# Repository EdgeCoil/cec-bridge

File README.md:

# cec-bridge

An HDMI-CEC and IR bridge for Home Assistant: an ESP32-C3 running ESPHome that plugs into a spare
port on a TV or AV receiver, talks CEC, and blasts and learns IR. 40 × 48 mm, two layers, every
part placed by the assembler.

- [`cec-bridge/`](cec-bridge/): the board, its generator and build, and the full README (what it
  does, how to build and order it, bring-up checks, firmware notes, credits and licence).
- [`vendor/`](vendor/): the [edgecoil-pcb](https://github.com/EdgeCoil/edgecoil-pcb) toolkit the
  board is built with, vendored so the board builds on its own.

Not yet built: the design is reviewed and simulated, but no boards have been ordered.

HDMI is a trademark of HDMI Licensing Administrator, Inc. This is an independent design, not a
licensed HDMI product.

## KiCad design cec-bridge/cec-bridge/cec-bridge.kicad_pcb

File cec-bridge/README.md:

# cec-bridge

An HDMI-CEC and IR bridge for Home Assistant: an ESP32-C3-WROOM-02 running ESPHome
(`Palakis/esphome-hdmi-cec`), on a short HDMI cable into a spare port on the TV or receiver. It
speaks CEC only (pin 13), reads hot-plug detect (pin 19) and can put +5 V on pin 18 for sinks that
only listen on a port that sees it. TMDS and DDC are not connected: no video, no EDID. It also blasts
IR (an on-board 940 nm LED and a JST-PH socket for a stick-on emitter) and has an IR receiver for
learning codes. Power is USB-C from a 5 V wall charger rated 1 A or more, on an always-on socket,
that holds USB's 4.75–5.25 V (simulated to 5.5 V: past 5.25 V pin 18 exceeds HDMI's 5.3 V, and a
contact bounce with pin 18 on can ring it to U6's 7 V limit).
Not the TV's or receiver's USB port: those give 500 mA and often switch off in standby, and Wi-Fi
transmit, IR and pin 18 together peak near 0.6 A (about 0.9 A with pin 18 shorted).

40 × 48 mm, two layers, every part on the top and placed by JLC; nothing to hand-solder.

## Build

```
KICAD_SYMBOL_DIR=~/.local/share/kicad-symbols/x/usr/share/kicad/symbols ./build.sh
```

`gen.py` writes the schematic and board, `route.py` replays the frozen routing in
`cec-bridge/routing.json` (move it aside to autoroute again, only after a placement change), and `build.sh` runs ERC/DRC
and writes JLC's BOM and placement files to `cec-bridge/fab/`. Reviewed in audit rounds until one came back clean, then simulated with the routed copper.

## Ordering

- JLC Standard PCBA, top side. If JLC adds rails, they go on the left and right edges: the module
  antenna overhangs the top edge and the USB-C face the bottom edge (by 0.46 mm).
- JLC's DFM check flags the USB-C shell slots (0.6 mm, below its 0.61 mm alert). They are the
  connector's own figure and JLC drills them; the alert is expected.
- The board edge runs about 0.3 mm past the HDMI socket's face (the USB-C face sits 0.46 mm proud of
  its edge). A plug's moulding tolerates about 1 mm of recess, so an enclosure wall in front of the
  socket should be thin there; seat a real cable at bring-up.
- H1 (the M2 hole beside the switches) has a 3V3 track 1.6 mm from its centre on the top, under
  mask: **nothing metal on the top there** — a nylon screw head, washer or
  standoff, or insert the screw from the back with a nylon washer on top. On the back the nearest
  copper is a 3V3 via 2.7 mm out (track 2.8 mm), so an M2 nut, 4 mm pan head or 4 mm hex standoff is
  fine on that side; not a washer (a DIN 125 sitting off-centre reaches the via).
- H2 has a VBUS track 2.85 mm from its centre on the top and ground otherwise: the same hardware as
  H1's back (M2 nut, 4 mm pan head or hex standoff), no metal washer on the top.
- The HDMI socket is held by its four shell legs. The enclosure should back the socket so plugging
  a cable in doesn't lever the board on its two M2 screws.
- **Stock, re-queried 2026-10-30.** U6 is a **TPS25200DRVT (C2653855)**: 484 listed, 167 orderable.
  The DRVR (C128401) listed 79 but was oversold (JLC's orderable figure -664; LCSC stock 0). Same part,
  small reel. J3 is an XYECONN XY-S2B-PH-SM4-TB (C54582899, about 5,000 orderable), a JST-PH-compatible
  2-pin SMD header; JST's own S2B-PH-SM4-TB (C295747) was down to 2. Every other line had at least
  6,397. **Check U6's orderable number (not the listed stock) before paying.**
- JLC's DFM check may flag same-net copper within 0.07 mm of a few pad openings: C11.1's opening is
  0.010 mm from its own VBUS track (also C10.2, C5.2 at 0.041 mm and TP1 at 0.051 mm). Same net,
  connected: expected.

## Bring-up checks

1. **Unpowered, it must not load the CEC bus** (HDMI 1.4: at most 1.8 µA). Every part on the line
   is chosen on its guaranteed figure: D1 is a BAV170 (a BAT54C passed 1.8 µA from about 37 °C in
   simulation) and the ESD array U3 a TPD4E1U06 (10 nA maximum at 2.5 V, where an SRV05-4 is specified to 5 µA;
   CEC idles at 3.3 V, far below its 6.5 V minimum breakdown).
   Unpowered, feed pin 13 from 3.3 V through 27 kΩ: the drop across the resistor must be under 49 mV.
2. **3V3 during Wi-Fi transmit:** scope it at the regulator and at the module. The output capacitance
   (C4, C5 and the module's own) is above the 22 µF ST characterises the LDL1117's stability for; the
   copper brings the ESR inside its range, and simulation can't prove the phase margin. Look for
   ringing on power-up and on a Wi-Fi burst, with a ground spring. Both capacitors are unlabelled:
   - **At the regulator:** C4 is the 0805 just above U5, left of R25 (the labelled 0603). **Don't
     probe across C4:** its right pad is its return (net C4_ESR), which reaches ground only through
     R25, so once R25 is swapped the probe would miss the ringing. Probe from C4's left pad (3V3) to
     R25's right pad (GND), 5.2 mm apart; U5's pin 1 (GND), 5.0 mm away, also works.
   - **At the module:** C5 is the 0603 in the top-left corner, left of the module's pin 1; its upper
     pad is GND and its lower pad 3V3, 1.55 mm apart.

   If 3V3 rings or oscillates, **swap R25** (0 Ω, in C4's return) for 0.1–0.47 Ω: that puts C4's ESR
   well inside ST's Fig. 20/21 region without a new board. Use tweezers or an iron, not hot air: C4's
   pad is 0.78 mm away and would lift too. Re-scope after the swap. If that is not enough, ST's other
   lever is C4 down to 4.7–10 µF.
3. **Pin 18 with the switch on** follows VBUS to within about 10 mV (U6, a TPS25200, is a 60 mΩ
   switch), so it is the charger's voltage: USB allows 4.75–5.25 V, so only a charger at the very
   bottom of that range puts it under HDMI's 4.8 V minimum. U6 limits the current to 240–350 mA
   (R24 330k; HDMI asks for at most 0.5 A), soft-starts in 2–3 ms, and never back-feeds VBUS while
   off (while on it conducts both ways: a sink driving pin 18 can feed the board). On a held short it
   holds the limit and cycles on its thermal shutdown; the instant a short lands, VBUS dips for
   microseconds while U6's limit catches up (sim4: 3V3 down to 3.03 V on the real copper, below
   3.0 V in a lumped model), so the ESP32 may reset once. That is acceptable for a fault.
   Its input is rated to 20 V, so VBUS ringing to about 9 V at plug-in can't hurt it; above
   6.8–8.45 V it disconnects pin 18, and it clamps pin 18 at 5.25–5.55 V.
   R16 holds it off through reset (IO5 has no pull of its own). Check: switch it on into a real sink,
   then short pin 18 to ground through an ammeter while scoping 3V3 at the module: about
   0.24–0.35 A once settled, and the board running (at most one reset as the short lands).
4. **IR**: the external emitter plugs into J3 with its anode on the pin marked "+" (pin 1, fed from
   VBUS through R20); JST-PH lead colours aren't consistent between suppliers. Each LED takes about 80 mA pulses through 47 Ω. The receiver sits 6 mm from the on-board
   LED and hears its own transmissions; ignore received codes while transmitting.

## Firmware notes

- Keep ESPHome's brown-out detector on (the default): a dropout of a few ms takes 3V3 low without
  EN ever resetting the chip.
- IR transmit: `carrier_duty_percent: 33` (ESPHome defaults to 50), which keeps R19 and R20 inside
  their 1/8 W even within a long burst.
- Debounce HPD (IO6, active low) for a few hundred ms: with a hot, low-threshold Q4 a source low
  near 0.6 V can read as half-asserted.

## Credits and licence

The footprints, symbols and 3D models in `lib/` (the HDMI socket, IR receiver, 2835 IR LED and
SOT-223 parts, and the `cb` symbols) come from the JLCEDA/EasyEDA official library
([lceda.cn](https://lceda.cn), [easyeda.com](https://easyeda.com)), converted with `easyeda2kicad`.
The 3D models are not included: fetch them with `easyeda2kicad --3d --lcsc_id=<part> --output lib/cb`
for the LCSC part numbers in the BOM.

The board design is CERN-OHL-S-2.0 and the scripts MIT, as each file's header says; `vendor/` is
the MIT-licensed [edgecoil-pcb](https://github.com/EdgeCoil/edgecoil-pcb) toolkit. The edgecoil name
and mark are not licensed.

HDMI, the HDMI logo and High-Definition Multimedia Interface are trademarks or registered trademarks
of HDMI Licensing Administrator, Inc. This is an independent hobby design, not a licensed HDMI
product, and is not affiliated with or endorsed by HDMI Licensing Administrator.

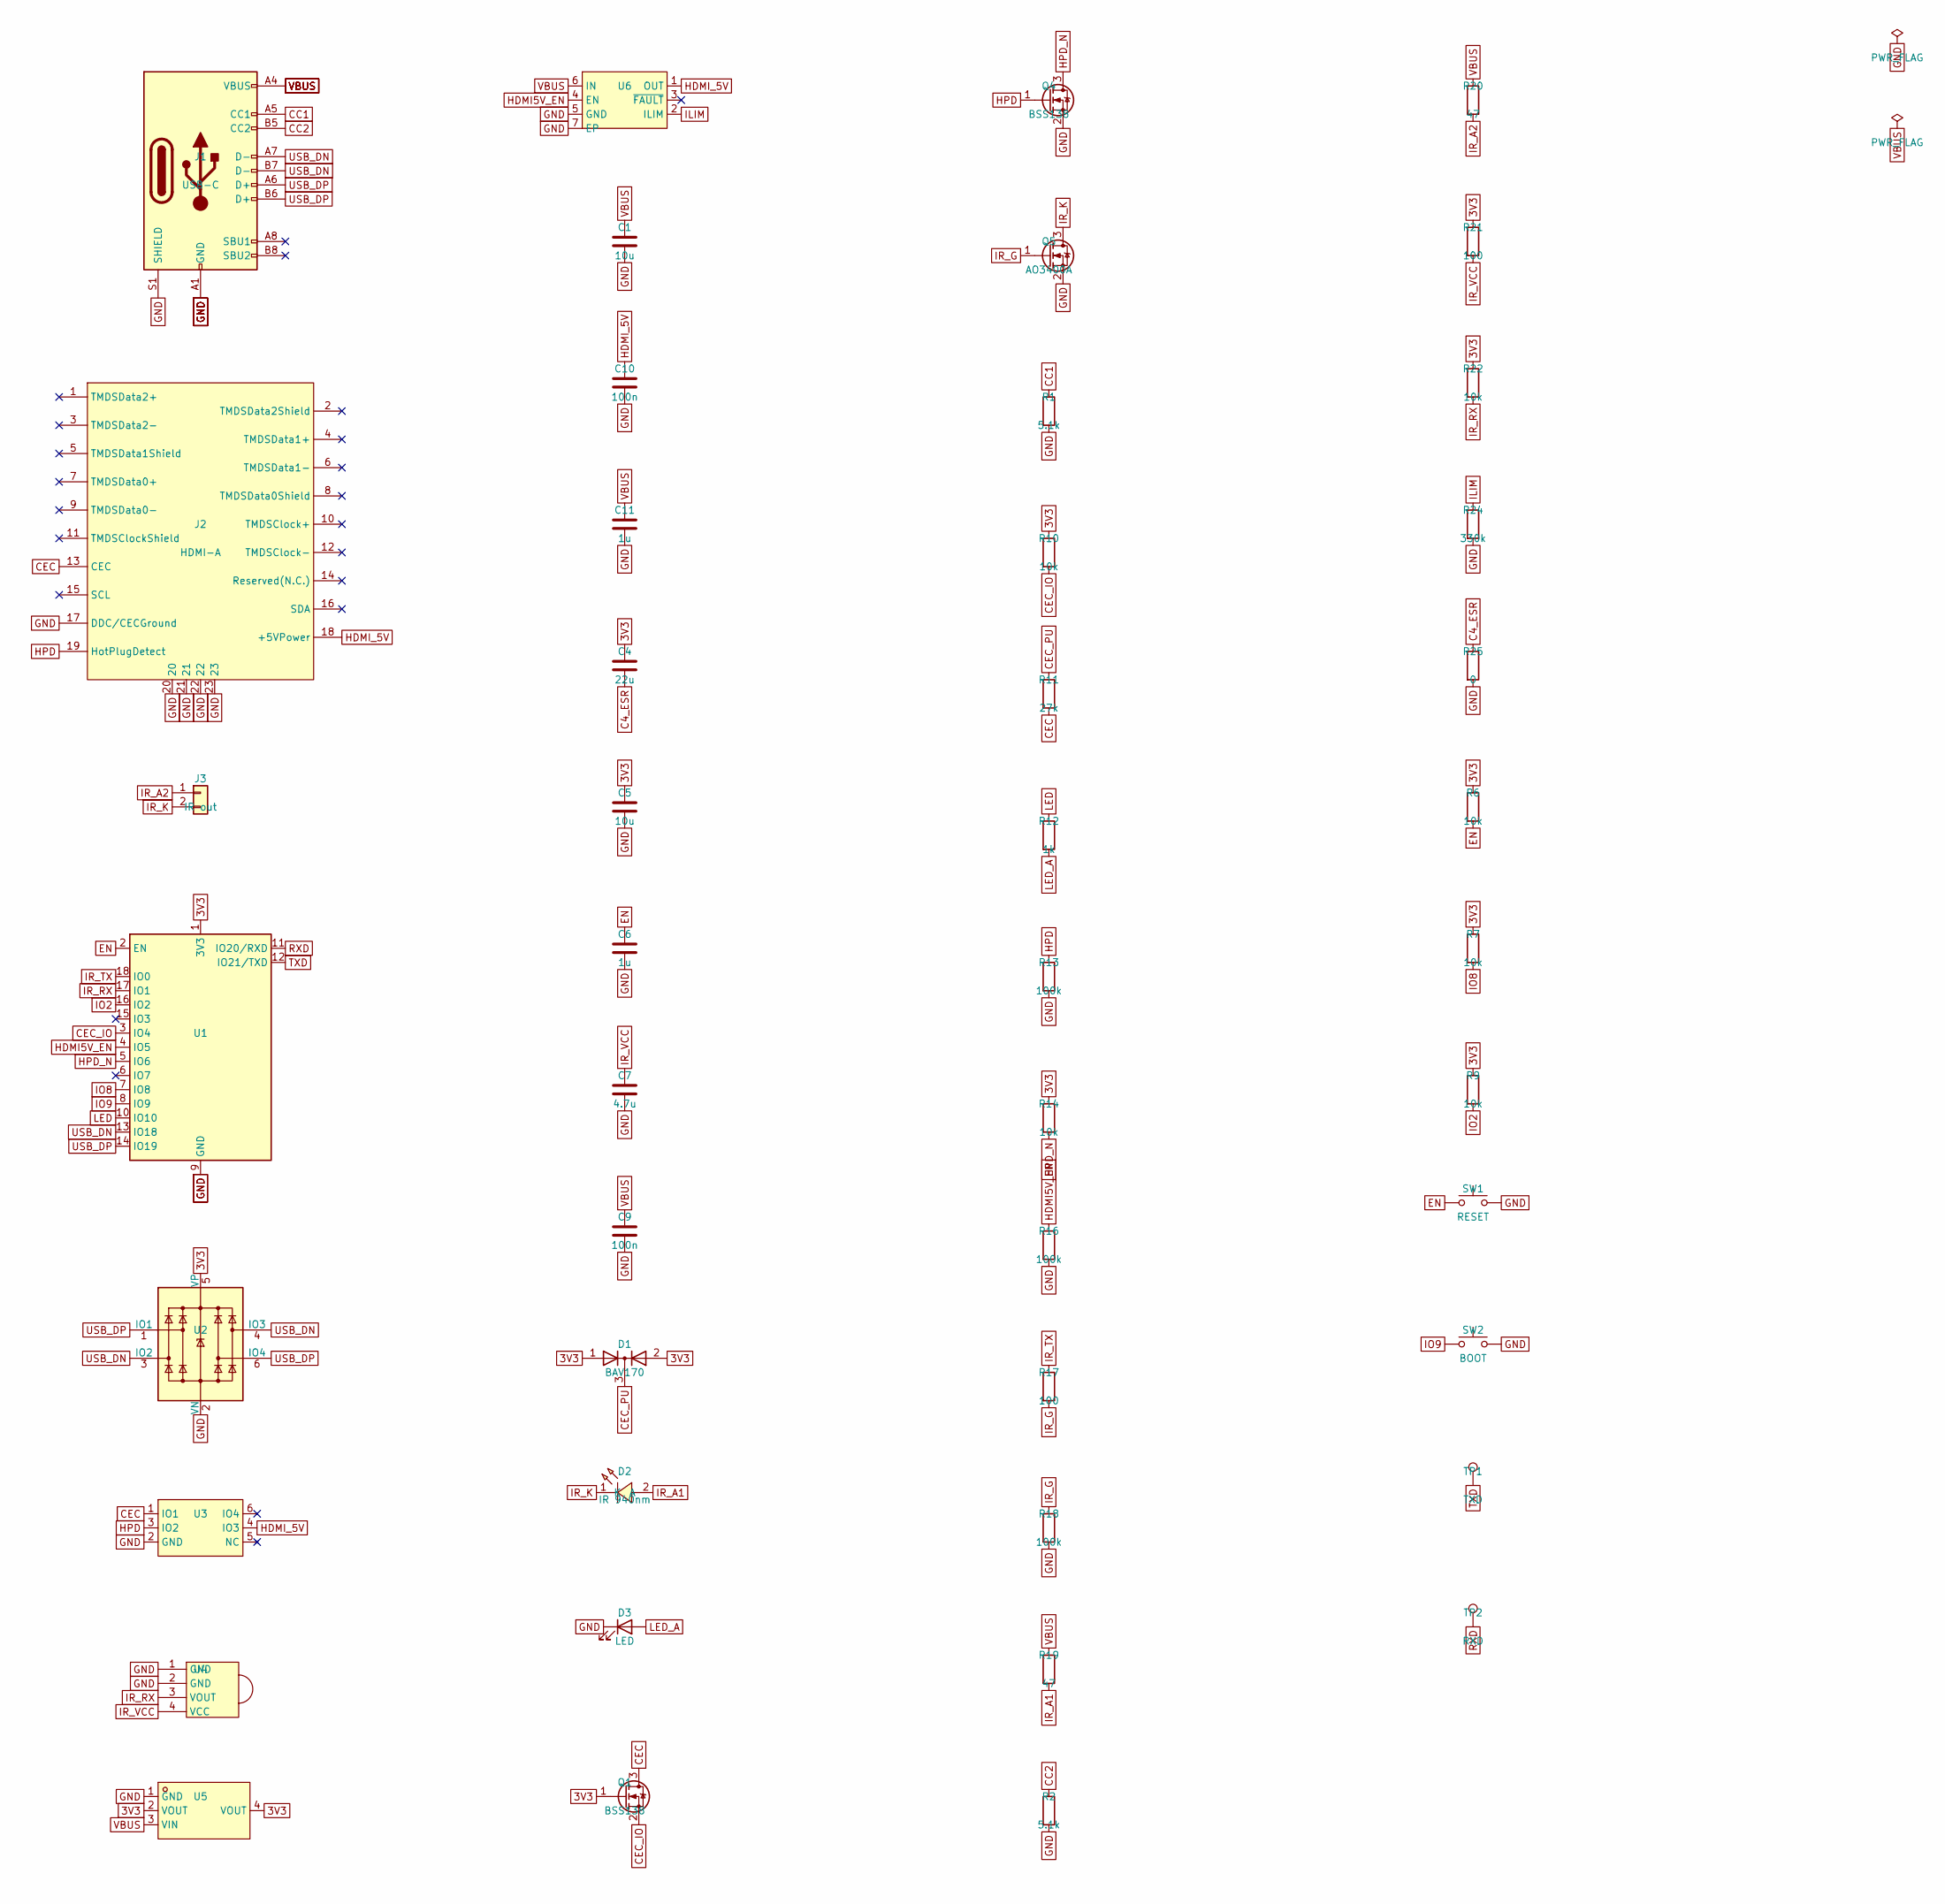
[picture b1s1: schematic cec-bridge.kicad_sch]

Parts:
C1: 10u; C_0805_2012Metric; LCSC C15850
C4: 22u; C_0805_2012Metric; LCSC C45783
C5: 10u; C_0603_1608Metric; LCSC C19702
C6, C11: 1u; C_0603_1608Metric; LCSC C15849
C7: 4.7u; C_0603_1608Metric; LCSC C19666
C9, C10: 100n; C_0603_1608Metric; LCSC C14663
D1: BAV170; SOT-23; MPN BAV170,215; LCSC C109309
D2: IR 940nm; LED-SMD_L3.5-W2.8_CZ2835; MPN P2835P1IRS7G12; LCSC C22466173
D3: LED; LED_0805_2012Metric; LCSC C84256
J1: USB-C; USB_C_Receptacle_HRO_TYPE-C-31-M-12; MPN HRO TYPE-C-31-M-12; LCSC C165948
J2: HDMI-A; HDMI-SMD_19P-P0.50-H-F; MPN HDMI-001 19PCBTP; LCSC C138388
J3: IR out; JST_PH_S2B-PH-SM4-TB_1x02-1MP_P2.00mm_Horizontal; MPN XYECONN XY-S2B-PH-SM4-TB; LCSC C54582899
Q1, Q4: BSS138; SOT-23; MPN BSS138LT1G; LCSC C82045
Q5: AO3400A; SOT-23; MPN AO3400A; LCSC C20917
R1, R2: 5.1k; R_0603_1608Metric; LCSC C23186
R6, R7, R9, R10, R14, R22: 10k; R_0603_1608Metric; LCSC C25804
R11: 27k; R_0603_1608Metric; LCSC C22967
R12: 1k; R_0603_1608Metric; LCSC C21190
R13, R16, R18: 100k; R_0603_1608Metric; LCSC C25803
R17, R21: 100; R_0603_1608Metric; LCSC C22775
R19, R20: 47; R_0805_2012Metric; LCSC C17714
R24: 330k; R_0603_1608Metric; LCSC C23137
R25: 0; R_0603_1608Metric; MPN 0603WAF0000T5E; LCSC C21189
SW1: RESET; SW_Push_1P1T_XKB_TS-1187A; MPN XKB TS-1187A-B-A-B; LCSC C318884
SW2: BOOT; SW_Push_1P1T_XKB_TS-1187A; MPN XKB TS-1187A-B-A-B; LCSC C318884
TP1: TXD; TestPoint_Pad_1.0x1.0mm
TP2: RXD; TestPoint_Pad_1.0x1.0mm
U1: ESP32-C3-WROOM-02-N4; ESP32-C3-WROOM-02; MPN ESP32-C3-WROOM-02-N4; LCSC C2934560
U2: SRV05-4; SOT-23-6; MPN SRV05-4-P-T7; LCSC C85364
U3: TPD4E1U06; SOT-23-6; MPN TPD4E1U06DBVR; LCSC C124691
U4: IRM-H638T; SENSOR-SMD_IRM-H638T-TR2-TL; MPN IRM-H638T/TR2; LCSC C91447
U5: LDL1117S33R; SOT-223-4_L6.5-W3.5-P2.30-LS7.0-BR; MPN LDL1117S33R; LCSC C435835
U6: TPS25200DRVT; WSON-6-1EP_2x2mm_P0.65mm_EP1x1.6mm; MPN TPS25200DRVT; LCSC C2653855

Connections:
3V3: C4.1, C5.1, D1.1 (A), D1.2 (A), Q1.1 (G), R6.1, R7.1, R9.1, R10.1, R14.1, R21.1, R22.1, U1.1 (3V3), U2.5 (VP), U5.2 (VOUT), U5.4 (VOUT)
C4_ESR: C4.2, R25.1
CC1: J1.A5 (CC1), R1.1
CC2: J1.B5 (CC2), R2.1
CEC: J2.13 (CEC), Q1.3 (D), R11.2, U3.1 (IO1)
CEC_IO: Q1.2 (S), R10.2, U1.3 (IO4)
CEC_PU: D1.3 (K), R11.1
EN: C6.1, R6.2, SW1.1, U1.2 (EN)
GND: C1.2, C5.2, C6.2, C7.2, C9.2, C10.2, C11.2, D3.1 (K), J1.A1 (GND), J1.A12 (GND), J1.B1 (GND), J1.B12 (GND), J1.S1 (SHIELD), J2.17 (DDC/CECGround), J2.20, J2.21, J2.22, J2.23, Q4.2 (S), Q5.2 (S), R1.2, R2.2, R13.2, R16.2, R18.2, R24.2, R25.2, SW1.2, SW2.2, U1.9 (GND), U1.19 (GND), U2.2 (VN), U3.2 (GND), U4.1 (GND), U4.2 (GND), U5.1 (GND), U6.5 (GND), U6.7 (EP)
HDMI5V_EN: R16.1, U1.4 (IO5), U6.4 (EN)
HDMI_5V: C10.1, J2.18 (+5VPower), U3.4 (IO3), U6.1 (OUT)
HPD: J2.19 (HotPlugDetect), Q4.1 (G), R13.1, U3.3 (IO2)
HPD_N: Q4.3 (D), R14.2, U1.5 (IO6)
ILIM: R24.1, U6.2 (ILIM)
IO2: R9.2, U1.16 (IO2)
IO8: R7.2, U1.7 (IO8)
IO9: SW2.1, U1.8 (IO9)
IR_A1: D2.2 (A), R19.2
IR_A2: J3.1, R20.2
IR_G: Q5.1 (G), R17.2, R18.1
IR_K: D2.1 (K), J3.2, Q5.3 (D)
IR_RX: R22.2, U1.17 (IO1), U4.3 (VOUT)
IR_TX: R17.1, U1.18 (IO0)
IR_VCC: C7.1, R21.2, U4.4 (VCC)
LED: R12.1, U1.10 (IO10)
LED_A: D3.2 (A), R12.2
RXD: TP2.1, U1.11 (IO20/RXD)
TXD: TP1.1, U1.12 (IO21/TXD)
USB_DN: J1.A7 (D-), J1.B7 (D-), U1.13 (IO18), U2.3 (IO2), U2.4 (IO3)
USB_DP: J1.A6 (D+), J1.B6 (D+), U1.14 (IO19), U2.1 (IO1), U2.6 (IO4)
VBUS: C1.1, C9.1, C11.1, J1.A4 (VBUS), J1.A9 (VBUS), J1.B4 (VBUS), J1.B9 (VBUS), R19.1, R20.1, U5.3 (VIN), U6.6 (IN)

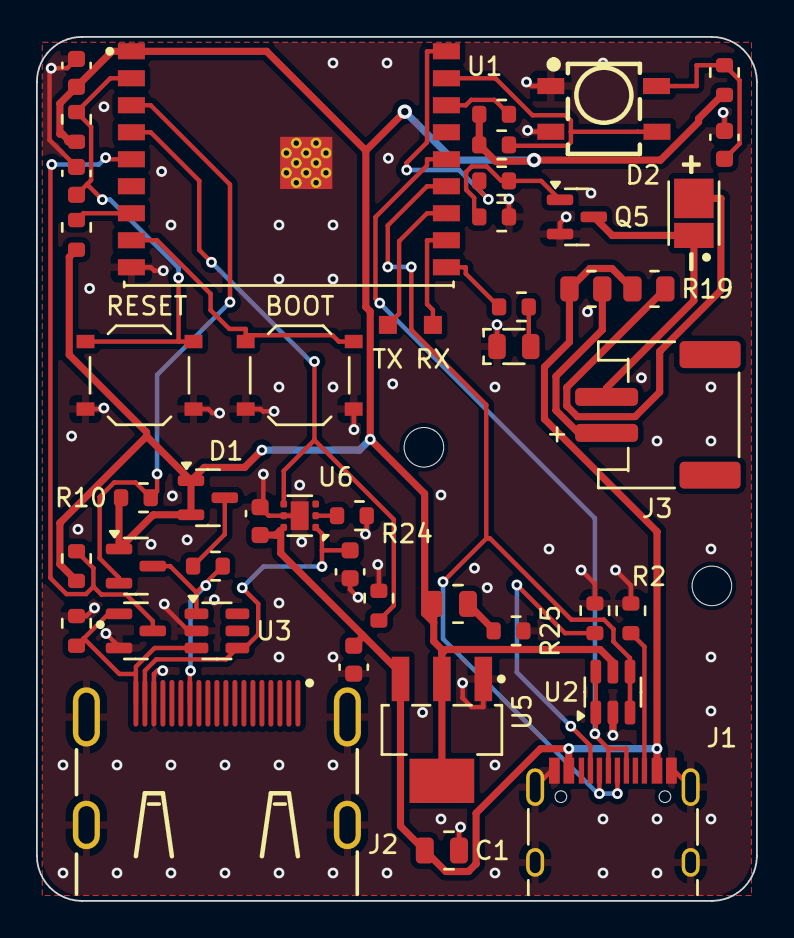
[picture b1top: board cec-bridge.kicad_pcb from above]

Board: 2 copper layers, 40.0 x 48.0 mm, 48 parts (0 on the bottom side), 31 nets.

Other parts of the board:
H1, H2: M2; MountingHole_2.2mm_M2
